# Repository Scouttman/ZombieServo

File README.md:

# ZombieServo
Motor Driver for some [aliexpress](https://www.aliexpress.com/item/1005004112490054.html) robotic serovos powered by simpleFOC and a STSPIN32g4
Runs simpleFOC forum post [here](https://community.simplefoc.com/t/zombie-servo-budget-high-torque-servo/4001)  
May also port the mit mini cheeta code to it if the torque control is good   
Position can be set with T i.e. set T6.28 will do one rotation (not sure why it is not a full rotation)  
The M command for simple foc is added but not tested

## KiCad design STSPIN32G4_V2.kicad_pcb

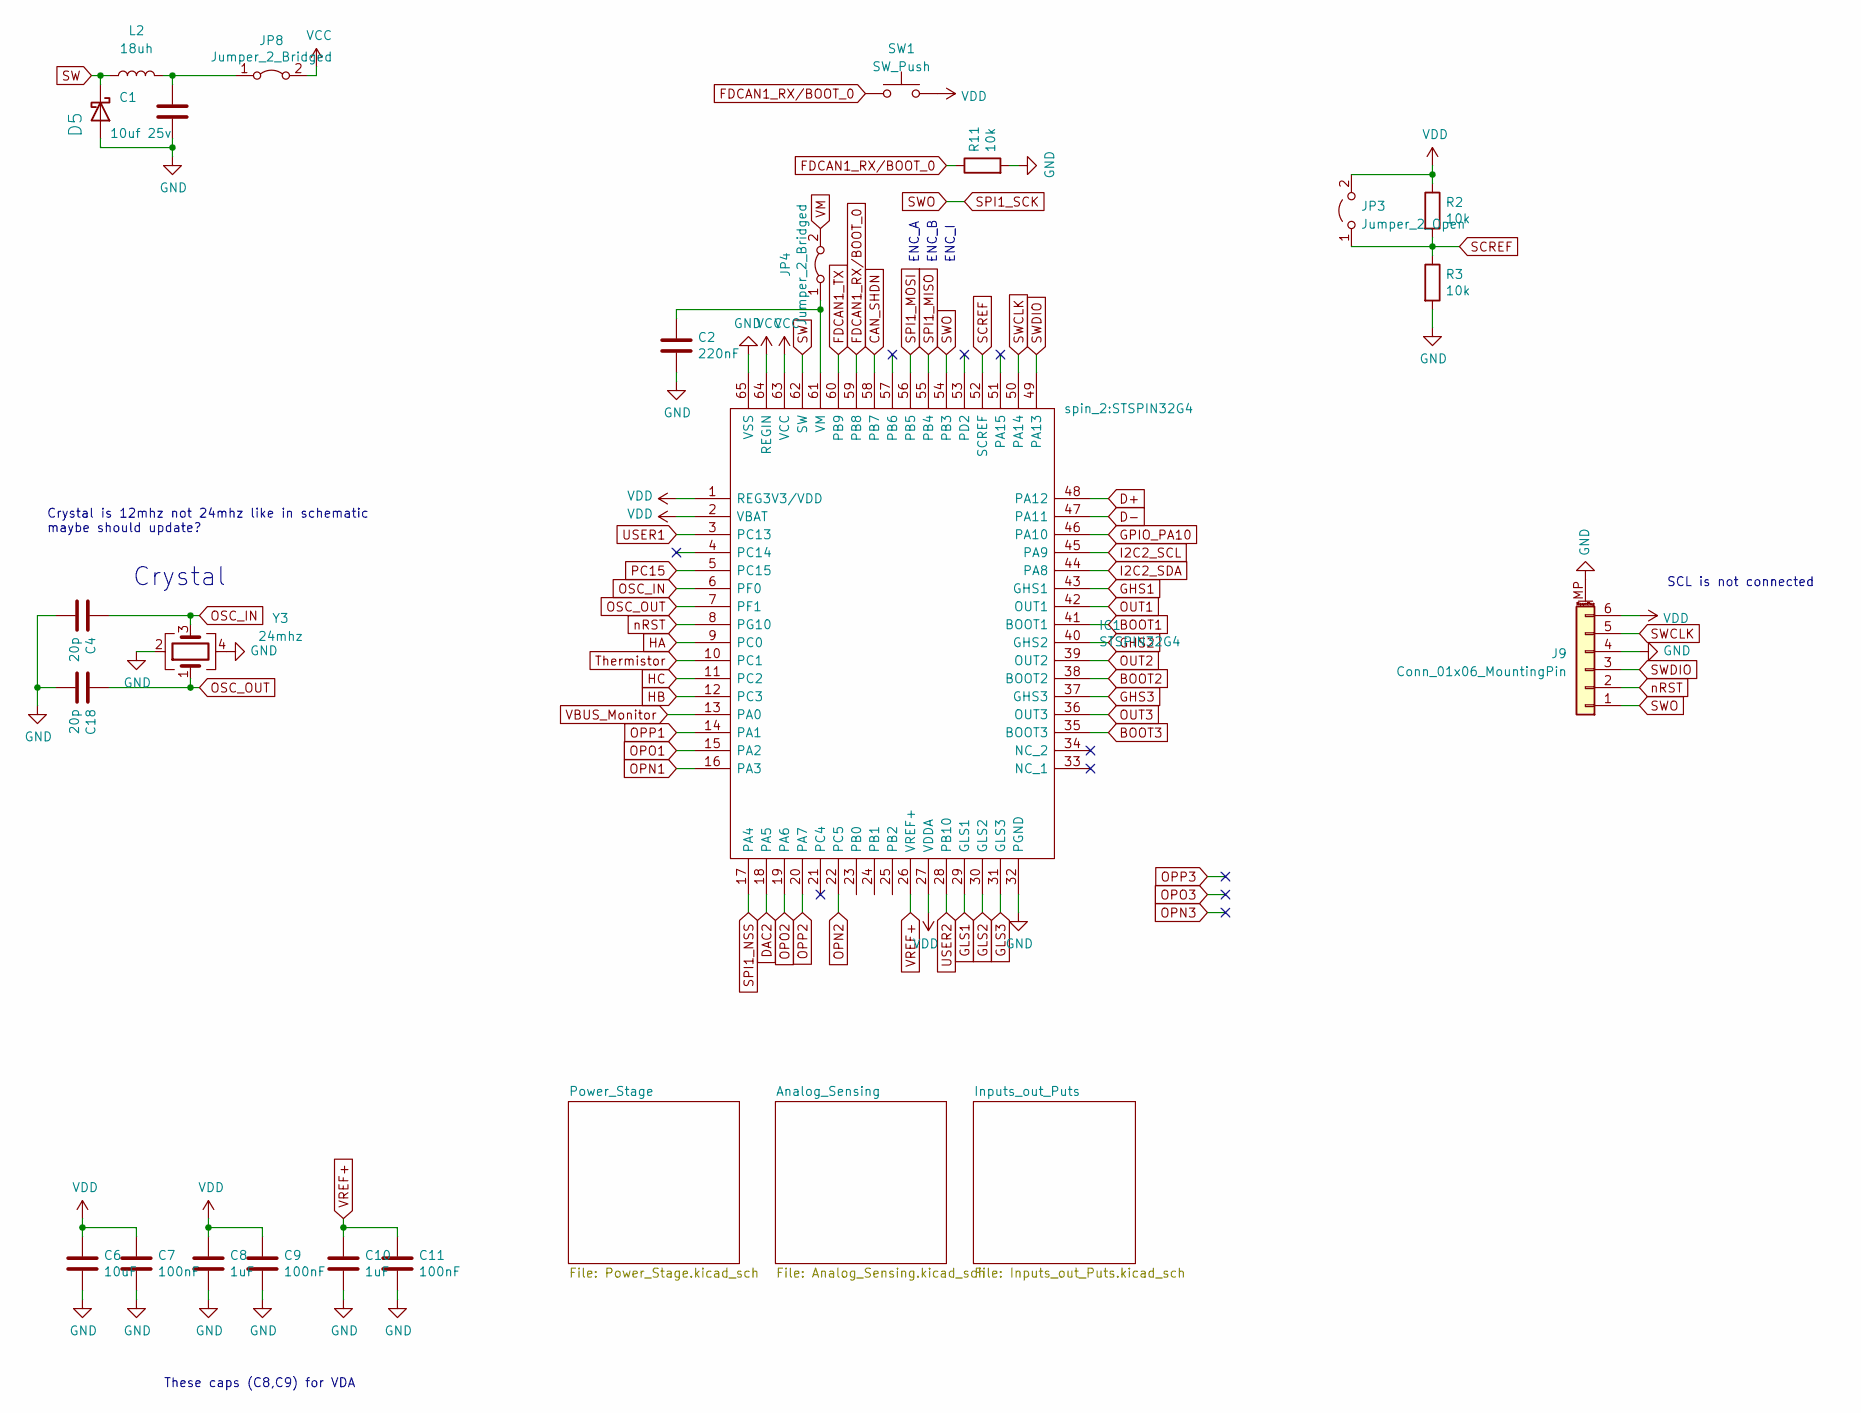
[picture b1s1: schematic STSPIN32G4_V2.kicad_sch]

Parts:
C1: 10uf 25v; C_0805_2012Metric
C2: 220nF; C_0805_2012Metric
C4, C18: 20p; C_0402_1005Metric
C6: 10uF; C_0805_2012Metric; LCSC Part C15850
C7, C9, C11: 100nF; C_0402_1005Metric
C8, C10: 1uF; C_0402_1005Metric
D5: SS210; D_SOD-323; LCSC C191023
IC1: STSPIN32G4; Manufacturer_Part_Number STSPIN32G4; Mouser Part Number 511-STSPIN32G4
J9: Conn_01x06_MountingPin; JST_SH_BM06B-SRSS-TB_1x06-1MP_P1.00mm_Vertical
JP3: Jumper_2_Open; SolderJumper-2_P1.3mm_Open_TrianglePad1.0x1.5mm
JP4, JP8: Jumper_2_Bridged; SolderJumper-2_P1.3mm_Bridged_RoundedPad1.0x1.5mm
L2: 18uh; L_1812_4532Metric; LCSC C394124
R2, R3, R11: 10k; R_0402_1005Metric
SW1: SW_Push; SolderJumper-2_P1.3mm_Open_RoundedPad1.0x1.5mm
Y3: 24mhz; Crystal_SMD_3225-4Pin_3.2x2.5mm; LCSC C9002

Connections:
BOOT1: IC1.41 (BOOT1); also elsewhere on the board
BOOT2: IC1.38 (BOOT2); also elsewhere on the board
BOOT3: IC1.35 (BOOT3); also elsewhere on the board
CAN_SHDN: IC1.58 (PB7); also elsewhere on the board
D+: IC1.48 (PA12); also elsewhere on the board
D-: IC1.47 (PA11); also elsewhere on the board
DAC2: IC1.18 (PA5)
FDCAN1_RX/BOOT_0: IC1.59 (PB8), R11.1, SW1.1; also elsewhere on the board
FDCAN1_TX: IC1.60 (PB9); also elsewhere on the board
GHS1: IC1.43 (GHS1); also elsewhere on the board
GHS2: IC1.40 (GHS2); also elsewhere on the board
GHS3: IC1.37 (GHS3); also elsewhere on the board
GLS1: IC1.29 (GLS1); also elsewhere on the board
GLS2: IC1.30 (GLS2); also elsewhere on the board
GLS3: IC1.31 (GLS3); also elsewhere on the board
GND: C1.2, C2.2, C4.2, C6.2, C7.2, C8.2, C9.2, C10.2, C11.2, C18.2, D5.2 (A), IC1.32 (PGND), IC1.65 (VSS), J9.4, J9.MP (MountPin), R3.2, R11.2, Y3.2, Y3.4; also elsewhere on the board
GPIO_PA10: IC1.46 (PA10); also elsewhere on the board
HA: IC1.9 (PC0); also elsewhere on the board
HB: IC1.12 (PC3); also elsewhere on the board
HC: IC1.11 (PC2); also elsewhere on the board
I2C2_SCL: IC1.45 (PA9); also elsewhere on the board
I2C2_SDA: IC1.44 (PA8); also elsewhere on the board
unnamed: C1.1, JP8.1 (A), L2.2
OPN1: IC1.16 (PA3); also elsewhere on the board
OPN2: IC1.22 (PC5); also elsewhere on the board
OPO1: IC1.15 (PA2); also elsewhere on the board
OPO2: IC1.19 (PA6); also elsewhere on the board
OPP1: IC1.14 (PA1); also elsewhere on the board
OPP2: IC1.20 (PA7); also elsewhere on the board
OSC_IN: C4.1, IC1.6 (PF0), Y3.3
OSC_OUT: C18.1, IC1.7 (PF1), Y3.1
OUT1: IC1.42 (OUT1); also elsewhere on the board
OUT2: IC1.39 (OUT2); also elsewhere on the board
OUT3: IC1.36 (OUT3); also elsewhere on the board
PC15: IC1.5 (PC15)
SCREF: IC1.52 (SCREF), JP3.1 (A), R2.2, R3.1
SPI1_MISO: IC1.55 (PB4); also elsewhere on the board
SPI1_MOSI: IC1.56 (PB5); also elsewhere on the board
SPI1_NSS: IC1.17 (PA4); also elsewhere on the board
SPI1_SCK: IC1.54 (PB3), J9.1; also elsewhere on the board
SW: D5.1 (K), IC1.62 (SW), L2.1
SWCLK: IC1.50 (PA14), J9.5
SWDIO: IC1.49 (PA13), J9.3
Thermistor: IC1.10 (PC1); also elsewhere on the board
USER1: IC1.3 (PC13); also elsewhere on the board
USER2: IC1.28 (PB10); also elsewhere on the board
VBUS_Monitor: IC1.13 (PA0); also elsewhere on the board
VCC: IC1.63 (VCC), IC1.64 (REGIN), JP8.2 (B)
VDD: C6.1, C7.1, C8.1, C9.1, IC1.1 (REG3V3/VDD), IC1.2 (VBAT), IC1.27 (VDDA), J9.6, JP3.2 (B), R2.1, SW1.2; also elsewhere on the board
VREF+: C10.1, C11.1, IC1.26 (VREF+); also elsewhere on the board
nRST: IC1.8 (PG10), J9.2

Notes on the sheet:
ENC_I
These caps (C8,C9) for VDA
ENC_B
Crystal
ENC_A
Crystal is 12mhz not 24mhz like in schematic maybe should update?
SCL is not connected

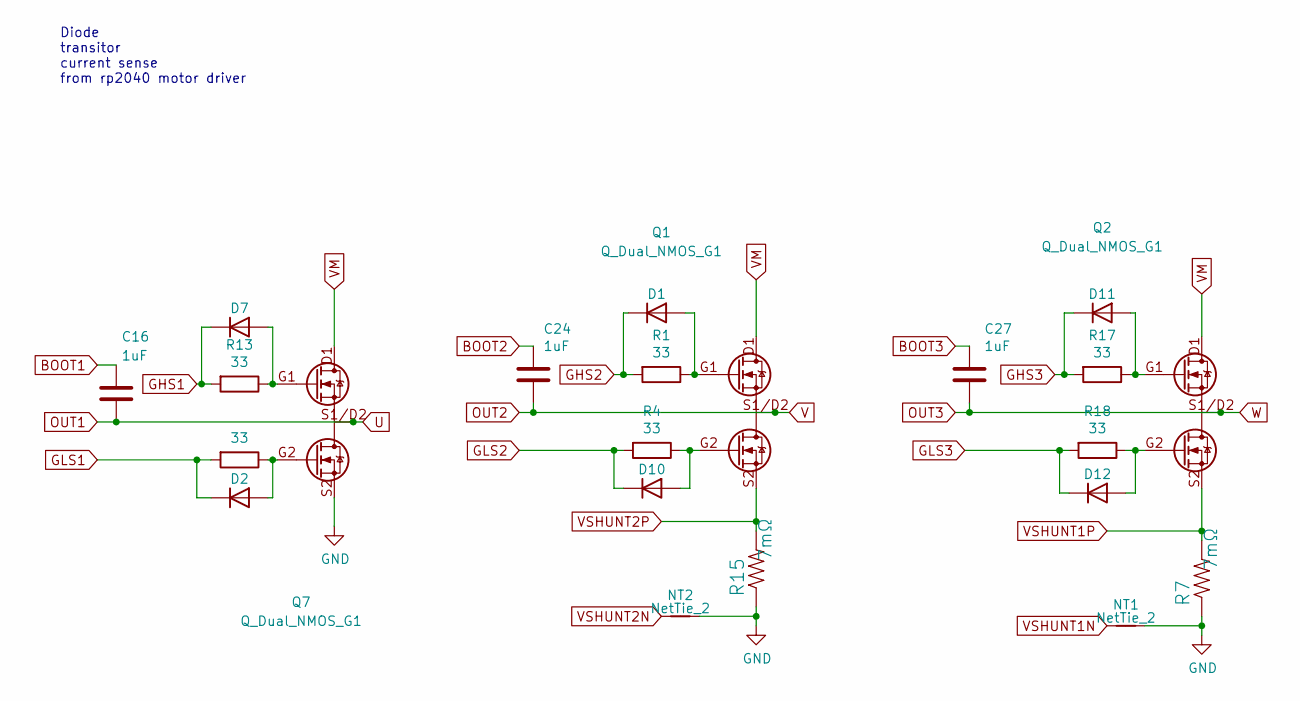
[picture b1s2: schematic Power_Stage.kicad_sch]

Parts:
C16, C24, C27: 1uF; C_0805_2012Metric; LCSC Part C28323
D1, D2, D7, D10, D11, D12: 1N4148WS; D_SOD-323; LCSC C2128
NT1, NT2: NetTie_2; NetTie-2_SMD_Pad0.5mm
Q1, Q2, Q7: Q_Dual_NMOS_G1; V-DFN3030-8 (Type K)
R1, R4, R13, R17, R18, R25: 33; R_0402_1005Metric
R7, R15: 7mΩ; R_1206_3216Metric; LCSC C76302

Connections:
BOOT1: C16.2; also elsewhere on the board
BOOT2: C24.2; also elsewhere on the board
BOOT3: C27.2; also elsewhere on the board
GHS1: D7.1 (K), R13.2; also elsewhere on the board
GHS2: D1.1 (K), R1.2; also elsewhere on the board
GHS3: D11.1 (K), R17.2; also elsewhere on the board
GLS1: D2.1 (K), R25.2; also elsewhere on the board
GLS2: D10.1 (K), R4.2; also elsewhere on the board
GLS3: D12.1 (K), R18.2; also elsewhere on the board
GND: NT1.2, NT2.2, Q7.S2, R7.1, R15.1; also elsewhere on the board
unnamed: D1.2 (A), Q1.G1, R1.1
unnamed: D2.2 (A), Q7.G2, R25.1
unnamed: D7.2 (A), Q7.G1, R13.1
unnamed: D10.2 (A), Q1.G2, R4.1
unnamed: D11.2 (A), Q2.G1, R17.1
unnamed: D12.2 (A), Q2.G2, R18.1
OUT1: C16.1, Q7.S1/D2; also elsewhere on the board
OUT2: C24.1, Q1.S1/D2; also elsewhere on the board
OUT3: C27.1, Q2.S1/D2; also elsewhere on the board
VSHUNT1N: NT1.1; also elsewhere on the board
VSHUNT1P: Q2.S2, R7.2; also elsewhere on the board
VSHUNT2N: NT2.1; also elsewhere on the board
VSHUNT2P: Q1.S2, R15.2; also elsewhere on the board

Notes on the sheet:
Diode transitor current sense from rp2040 motor driver

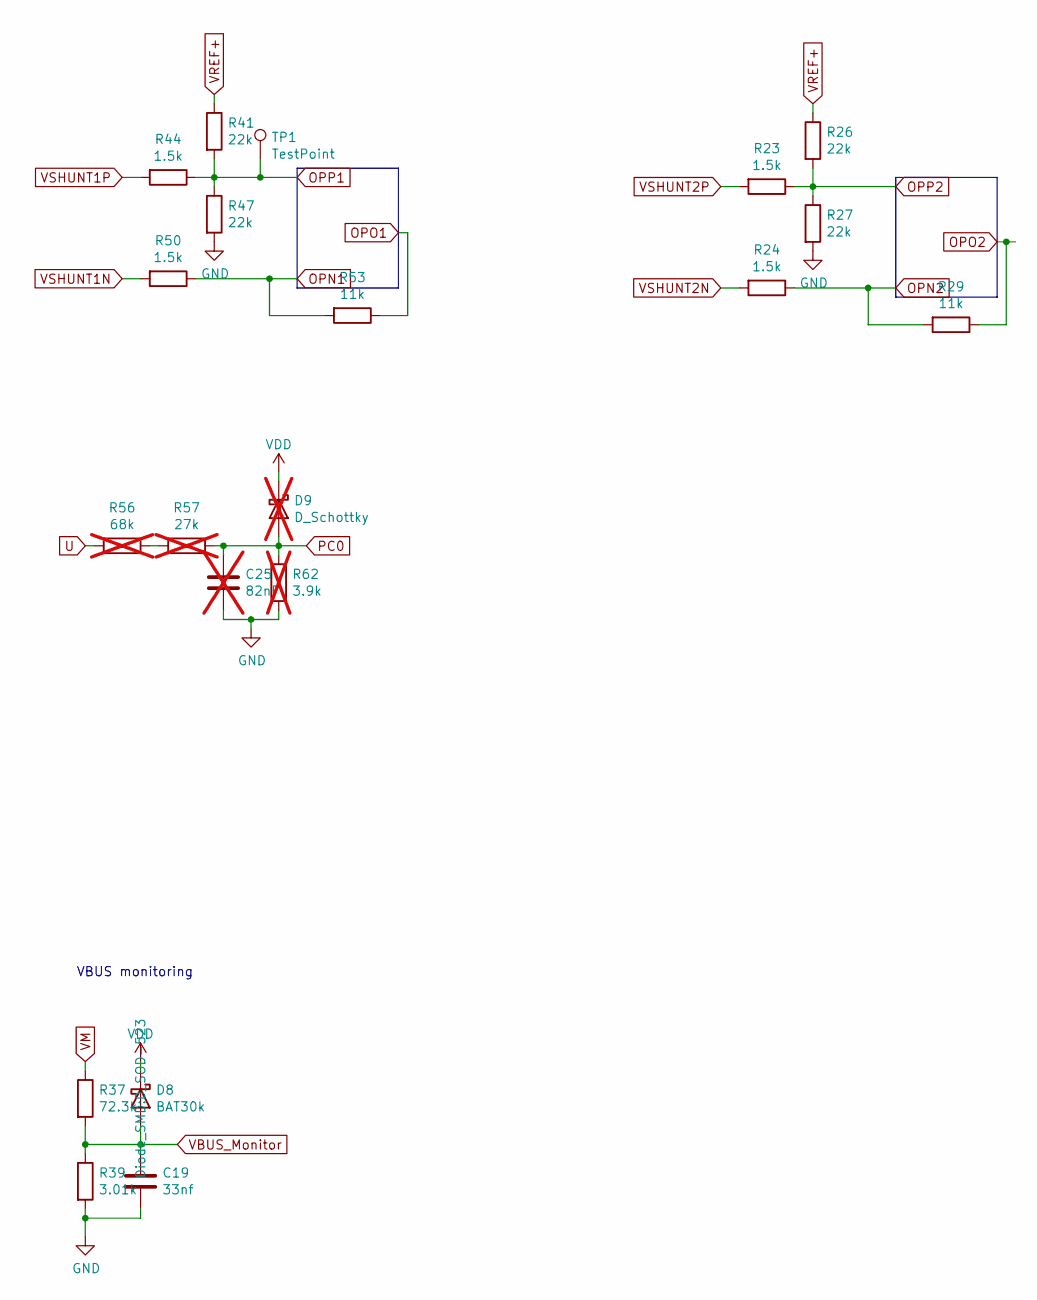
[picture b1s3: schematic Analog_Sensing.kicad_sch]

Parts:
C19: 33nf; C_0402_1005Metric
C25: 82nF; C_0402_1005Metric; not fitted
D8: BAT30k; D_SOD-523
D9: D_Schottky; D_SOD-523; not fitted
R23, R24, R44, R50: 1.5k; R_0402_1005Metric
R26, R27, R41, R47: 22k; R_0402_1005Metric
R29, R53: 11k; R_0402_1005Metric; LCSC C409665
R37: 72.3k; R_0402_1005Metric
R39: 3.01k; R_0402_1005Metric
R56: 68k; R_0402_1005Metric; not fitted
R57: 27k; R_0402_1005Metric; not fitted
R62: 3.9k; R_0402_1005Metric; not fitted
TP1: TestPoint; TestPoint_Pad_D2.0mm

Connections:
GND: C19.2, C25.2, R27.2, R39.2, R47.2, R62.2; also elsewhere on the board
unnamed: C25.1, D9.2 (A), R57.1, R62.1
unnamed: R56.1, R57.2
OPN1: R50.1, R53.2; also elsewhere on the board
OPN2: R24.1, R29.2; also elsewhere on the board
OPO1: R53.1; also elsewhere on the board
OPO2: R29.1; also elsewhere on the board
OPP1: R41.2, R44.1, R47.1, TP1.1; also elsewhere on the board
OPP2: R23.1, R26.2, R27.1; also elsewhere on the board
VBUS_Monitor: C19.1, D8.2 (A), R37.2, R39.1; also elsewhere on the board
VDD: D8.1 (K), D9.1 (K); also elsewhere on the board
VREF+: R26.1, R41.1; also elsewhere on the board
VSHUNT1N: R50.2; also elsewhere on the board
VSHUNT1P: R44.2; also elsewhere on the board
VSHUNT2N: R24.2; also elsewhere on the board
VSHUNT2P: R23.2; also elsewhere on the board

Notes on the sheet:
VBUS monitoring

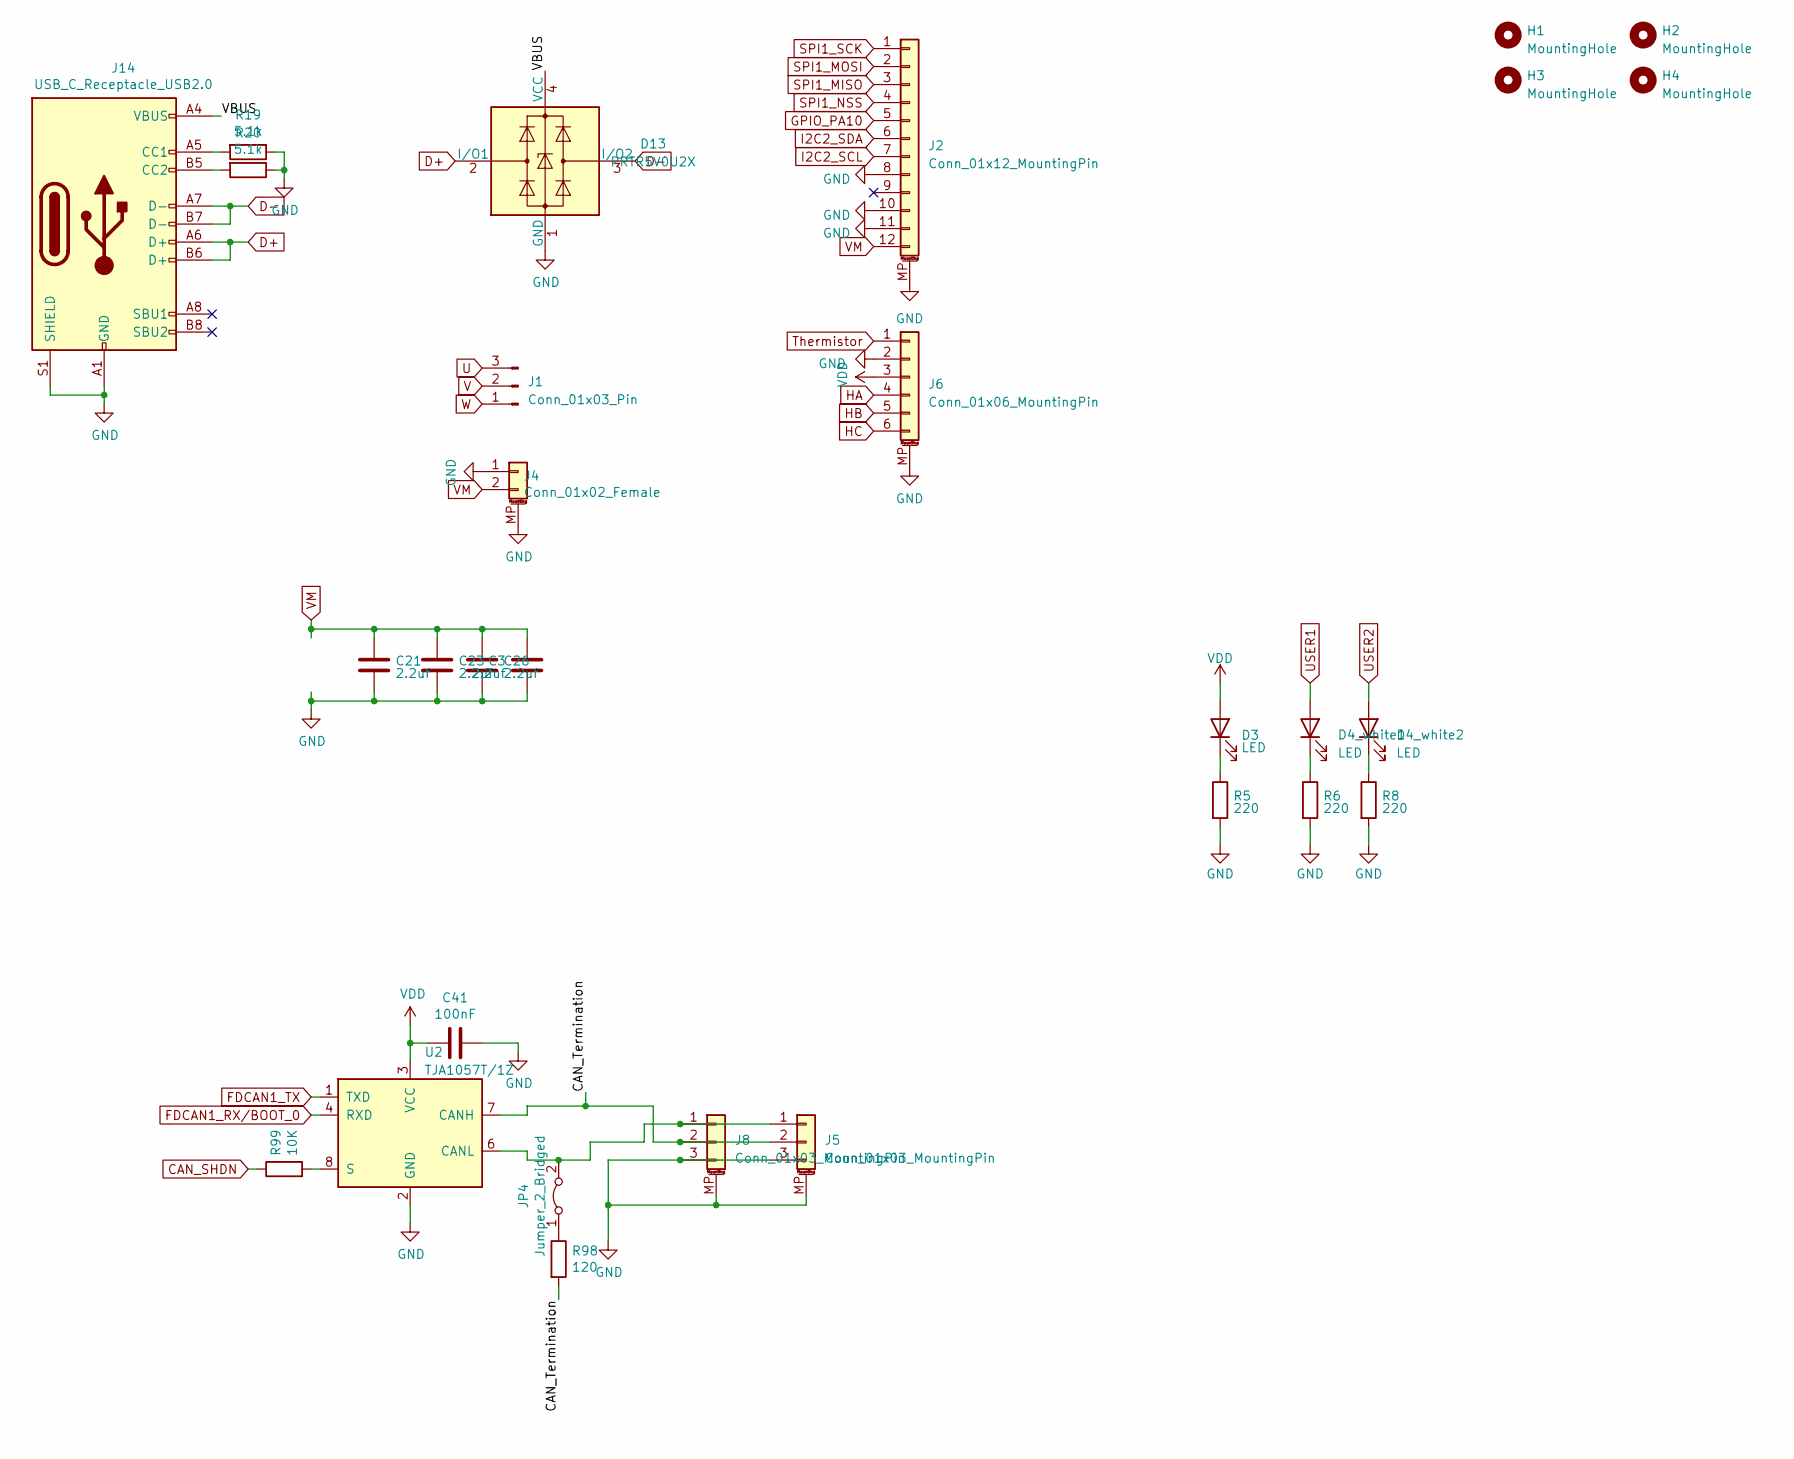
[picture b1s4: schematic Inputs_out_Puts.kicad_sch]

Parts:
C3, C21, C23, C26: 2.2uf; C_1206_3216Metric; LCSC Part C650969
C41: 100nF; C_0402_1005Metric
D3, D4_white1, D4_white2: LED; LED_0805_2012Metric
D13: PRTR5V0U2X; SOT-143
H1, H2, H3, H4: MountingHole; MountingHole_2.2mm_M2
J1: Conn_01x03_Pin; JST_XH_B3B-XH-AM_1x03_P2.50mm_Vertical
J2: Conn_01x12_MountingPin; 0.5K-A-12PBF; LCSC C2914207
J4: Conn_01x02_Female; PinHeader_1x02_P2.54mm_Vertical
J5, J8: Conn_01x03_MountingPin; JST_SH_BM03B-SRSS-TB_1x03-1MP_P1.00mm_Vertical
J6: Conn_01x06_MountingPin; PinHeader_1x06_P1.27mm_Vertical; LCSC C2904934
J14: USB_C_Receptacle_USB2.0; USB_C_Receptacle_XKB_U262-16XN-4BVC11; LCSC Part C165948
JP4: Jumper_2_Bridged; SolderJumper-2_P1.3mm_Bridged_RoundedPad1.0x1.5mm
R5, R6, R8: 220; R_0402_1005Metric
R19: 5.1k; R_0402_1005Metric
R20: 5.1k; R_0402_1005Metric; LCSC Part C23186
R98: 120; R_0402_1005Metric
R99: 10K; R_0402_1005Metric
U2: TJA1057T/1Z; SOIC-8_3.9x4.9mm_P1.27mm; LCSC C961484

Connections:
/Inputs_out_Puts/CAN_Termination: J5.2, J8.2, R98.2, U2.7 (CANH)
/Inputs_out_Puts/VBUS: D13.4 (VCC), J14.A4 (VBUS), J14.A9 (VBUS), J14.B4 (VBUS), J14.B9 (VBUS)
CAN_SHDN: R99.1; also elsewhere on the board
D+: D13.2 (I/O1), J14.A6 (D+), J14.B6 (D+); also elsewhere on the board
D-: D13.3 (I/O2), J14.A7 (D-), J14.B7 (D-); also elsewhere on the board
FDCAN1_RX/BOOT_0: U2.4 (RXD); also elsewhere on the board
FDCAN1_TX: U2.1 (TXD); also elsewhere on the board
GND: C3.2, C21.2, C23.2, C26.2, C41.1, D13.1 (GND), J2.8, J2.10, J2.11, J2.MP (MountPin), J4.1, J4.MP (MountPin), J5.3, J5.MP (MountPin), J6.2, J6.MP (MountPin), J8.3, J8.MP (MountPin), J14.A1 (GND), J14.A12 (GND), J14.B1 (GND), J14.B12 (GND), J14.S1 (SHIELD), R5.2, R6.2, R8.2, R19.1, R20.1, U2.2 (GND); also elsewhere on the board
GPIO_PA10: J2.5; also elsewhere on the board
HA: J6.4; also elsewhere on the board
HB: J6.5; also elsewhere on the board
HC: J6.6; also elsewhere on the board
I2C2_SCL: J2.7; also elsewhere on the board
I2C2_SDA: J2.6; also elsewhere on the board
unnamed: D3.1 (K), R5.1
unnamed: D4_white1.1 (K), R6.1
unnamed: D4_white2.1 (K), R8.1
unnamed: J14.A5 (CC1), R19.2
unnamed: J14.B5 (CC2), R20.2
unnamed: R99.2, U2.8 (S)
OUT1: J1.3; also elsewhere on the board
OUT2: J1.2; also elsewhere on the board
OUT3: J1.1; also elsewhere on the board
SPI1_MISO: J2.3; also elsewhere on the board
SPI1_MOSI: J2.2; also elsewhere on the board
SPI1_NSS: J2.4; also elsewhere on the board
SPI1_SCK: J2.1; also elsewhere on the board
Thermistor: J6.1; also elsewhere on the board
USER1: D4_white1.2 (A); also elsewhere on the board
USER2: D4_white2.2 (A); also elsewhere on the board
VDD: C41.2, D3.2 (A), J6.3, U2.3 (VCC); also elsewhere on the board

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
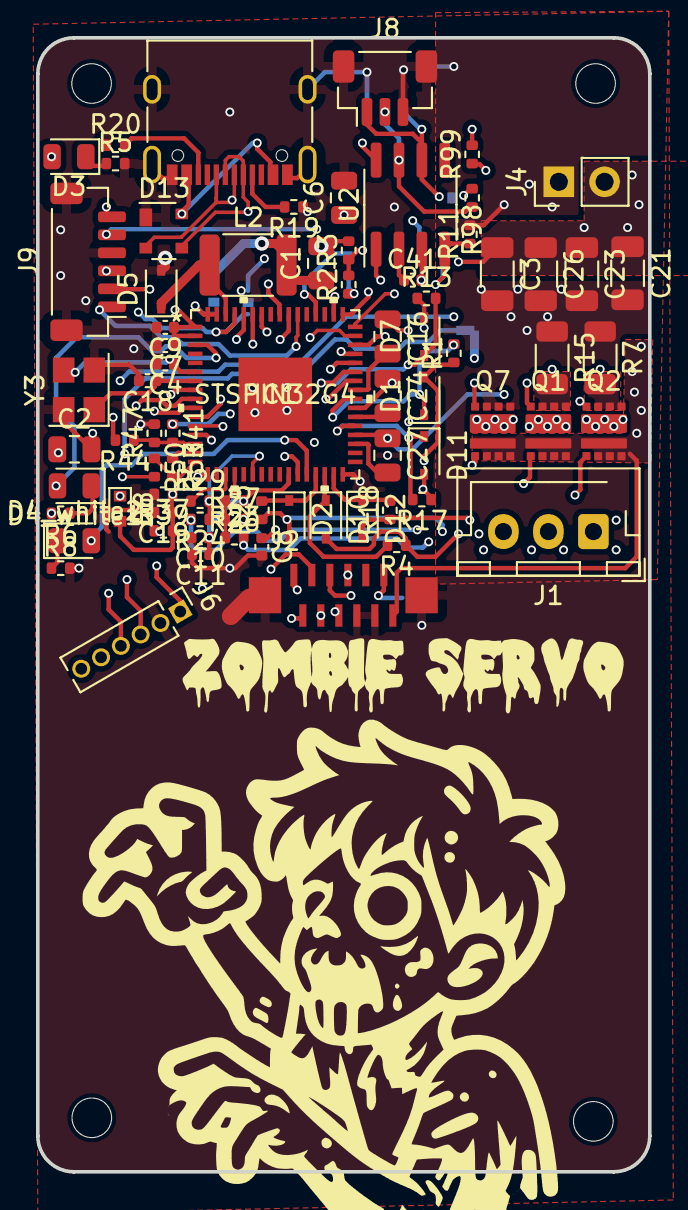
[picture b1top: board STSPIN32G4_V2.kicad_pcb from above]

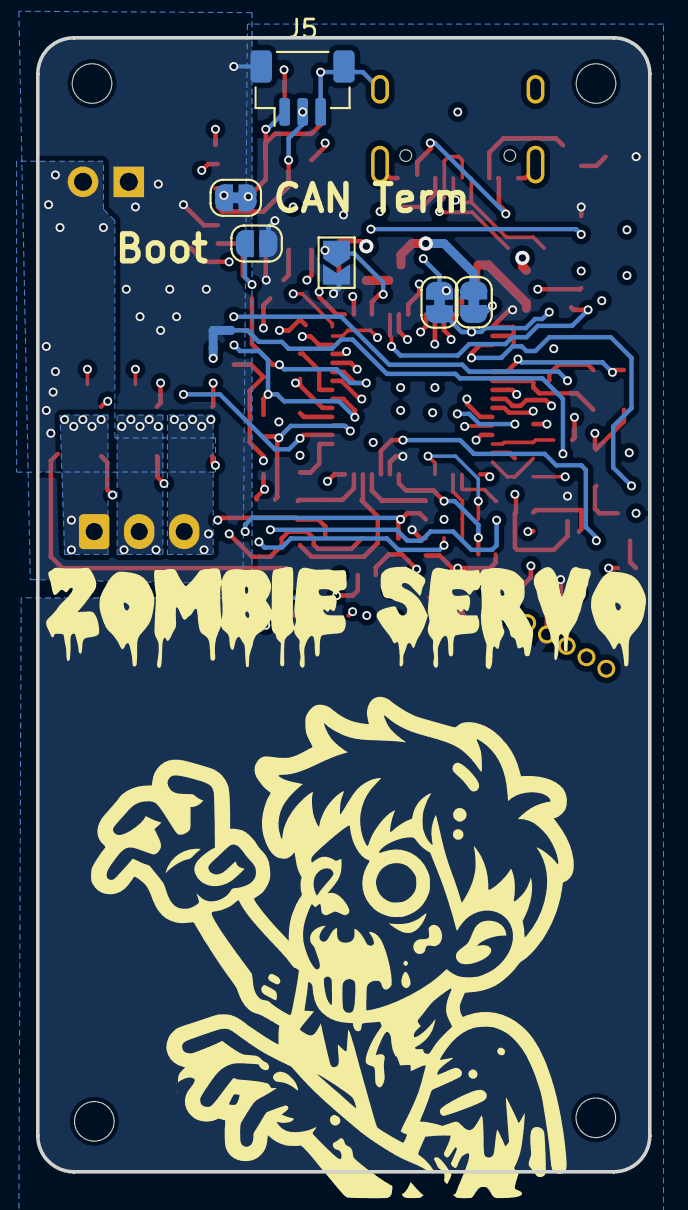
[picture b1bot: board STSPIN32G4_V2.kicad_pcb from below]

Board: 4 copper layers, 34.0 x 63.0 mm, 87 parts (8 on the bottom side), 71 nets.

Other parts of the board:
JP1: Jumper_2_Bridged; SolderJumper-2_P1.3mm_Bridged_RoundedPad1.0x1.5mm

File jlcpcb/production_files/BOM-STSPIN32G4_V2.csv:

Comment,Designator,Footprint,LCSC
Conn_01x03_MountingPin,J8,JST_SH_BM03B-SRSS-TB_1x03-1MP_P1.00mm_Vertical,C145955
Conn_01x06_MountingPin,J9,JST_SH_BM06B-SRSS-TB_1x06-1MP_P1.00mm_Vertical,C145958
20p,"C18,C4",C_0402_1005Metric,C1554
Q_Dual_NMOS_G1,"Q1,Q2,Q7",V-DFN3030-8 (Type K),C155503
33nf,C19,C_0402_1005Metric,C1585
10uf 25v,"C1,C6",C_0805_2012Metric,C15850
USB_C_Receptacle_USB2.0,J14,USB_C_Receptacle_XKB_U262-16XN-4BVC11,C165948
SS210,D5,D_SOD-323,C191023
1N4148WS,"D1,D10,D11,D12,D2,D7",D_SOD-323,C2128
LED,"D3,D4_white2",LED_0805_2012Metric,C2297
5.1k,R20,R_0402_1005Metric,C23186
120,R98,R_0402_1005Metric,C25079
220,"R5,R6,R8",R_0402_1005Metric,C25091
33,"R1,R13,R17,R18,R25,R4",R_0402_1005Metric,C25105
10k,"R11,R2,R3,R99",R_0402_1005Metric,C25744
22k,"R26,R27,R41,R47",R_0402_1005Metric,C25768
1.5k,"R23,R24,R44,R50",R_0402_1005Metric,C25867
5.1k,R19,R_0402_1005Metric,C25905
PRTR5V0U2X,D13,SOT-143,C2827688
1uF,"C16,C24,C27",C_0805_2012Metric,C28323
STSPIN32G4,IC1,STSPIN32G4,C2858620
Conn_01x06_MountingPin,J6,PinHeader_1x06_P1.27mm_Vertical,C2904934
Conn_01x12_MountingPin,J2,0.5K-A-12PBF,C2914207
BAT30k,D8,D_SOD-523,C2926449
100nF,"C11,C41,C7,C9",C_0402_1005Metric,C307331
18uh,L2,L_1812_4532Metric,C394124
11k,"R29,R53",R_0402_1005Metric,C409665
1uF,"C10,C8",C_0402_1005Metric,C52923
220nF,C2,C_0805_2012Metric,C5378
2.2uf,"C21,C23,C26,C3",C_1206_3216Metric,C650969
7mΩ,"R15,R7",R_1206_3216Metric,C76302
LED,D4_white1,LED_0805_2012Metric,C84256
24mhz,Y3,Crystal_SMD_3225-4Pin_3.2x2.5mm,C9002
TJA1057T/1Z,U2,SOIC-8_3.9x4.9mm_P1.27mm,C961484
Conn_01x02_Female,J4,PinHeader_1x02_P2.54mm_Vertical,
Jumper_2_Bridged,JP8,SolderJumper-2_P1.3mm_Bridged_RoundedPad1.0x1.5mm,
NetTie_2,NT1,NetTie-2_SMD_Pad0.5mm,
72.3k,R37,R_0402_1005Metric,
3.01k,R39,R_0402_1005Metric,
Jumper_2_Bridged,JP4,SolderJumper-2_P1.3mm_Bridged_RoundedPad1.0x1.5mm,
Jumper_2_Open,JP3,SolderJumper-2_P1.3mm_Open_TrianglePad1.0x1.5mm,
NetTie_2,NT2,NetTie-2_SMD_Pad0.5mm,
MountingHole,H3,MountingHole_2.2mm_M2,
MountingHole,H2,MountingHole_2.2mm_M2,
MountingHole,H1,MountingHole_2.2mm_M2,
MountingHole,H4,MountingHole_2.2mm_M2,
Conn_01x03_Pin,J1,JST_XH_B3B-XH-AM_1x03_P2.50mm_Vertical,
Conn_01x03_MountingPin,J5,JST_SH_BM03B-SRSS-TB_1x03-1MP_P1.00mm_Vertical,
SW_Push,SW1,SolderJumper-2_P1.3mm_Open_RoundedPad1.0x1.5mm,
Jumper_2_Bridged,JP1,SolderJumper-2_P1.3mm_Bridged_RoundedPad1.0x1.5mm,

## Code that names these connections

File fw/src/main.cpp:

#include <Arduino.h>
#include <SimpleFOC.h>
#include "drivers/stspin32g4/STSPIN32G4.h"
// #include "encoders/ma730/MA730.h"
#include "encoders/ma730/MagneticSensorMA730.h"

#define LED_WHITE PB_10 
#define LED_RED PC_13
#define MAG_CS PA4
#define MOIS_PIN PB5
#define MISO_PIN PB4
#define SCLK_PIN PB3
#define SSI_SSCK_FREQUENCY  10000       //SSI SSCK Clock frequency in Hz #TODO increase back to 100k

STSPIN32G4 driver = STSPIN32G4();
BLDCMotor motor = BLDCMotor(1); // for drive module
HallSensor sensor = HallSensor(PC0, PC2, PC3, 1);
MagneticSensorMA730 output_encoder = MagneticSensorMA730(MAG_CS);
// interrupt routine intialisation
void doA(){sensor.handleA();}
void doB(){sensor.handleB();}
void doC(){sensor.handleC();}

// External digital encoder
SPIClass SPI_1(MOIS_PIN, MISO_PIN, SCLK_PIN);
PIDController PID_ang{1000.0,0.0,0.0,0,5000}; // PID controller for the output angle

// angle set point variable
float target_angle = 0;
Commander command = Commander(Serial);
void doTarget(char* cmd) { command.scalar(&target_angle, cmd); }
void doMotor(char* cmd) { command.motor(&motor, cmd); }

int counter = 0;

void setup() {
  Serial.begin();
  Serial.println("Start");
  command.add('M',doMotor,"motor");
  // add target command T
  command.add('T', doTarget, "target angle");

  // setup timer 6 to count micro seconds as the micro second timer inside stduino is slow
  __HAL_RCC_TIM6_CLK_ENABLE();
  TIM6->PSC = HAL_RCC_GetPCLK1Freq()/1000000 - 1;
  TIM6->CR1 = TIM_CR1_CEN;

  /* Initialize all configured peripherals */
  pinMode(LED_WHITE, OUTPUT);
  pinMode(LED_RED, OUTPUT);
  
  // initialise encoder hardware
  sensor.init();
  sensor.enableInterrupts(doA, doB, doC);
  motor.linkSensor(&sensor);
  output_encoder.init(&SPI_1);

  // driver
  driver.voltage_power_supply = 17.0f;
  driver.voltage_limit = 17.0f;
  driver.init();
  motor.voltage_limit = driver.voltage_limit / 2.0f;
  motor.controller = MotionControlType::velocity;
  // set the torque control type
  motor.phase_resistance = 12.5; // 12.5 Ohms
  // set motion control loop to be used
  // motor.controller = MotionControlType::torque;
  motor.linkDriver(&driver);
  motor.init();

  motor.PID_velocity.P = 0.001f;
  motor.PID_velocity.I = 0.0f;
  motor.PID_velocity.D = 0;

  // initialize motor
  motor.init();
  // align encoder and start FOC
  motor.initFOC();
  // driver.voltage_limit = 6;

  Serial.println(F("Motor ready."));
  Serial.println(F("Set the target angle using serial terminal:"));
}

void loop() {
    // main FOC algorithm function
  motor.loopFOC();
  
  float vel_set = PID_ang(output_encoder.getAngle()-target_angle);
  motor.move(vel_set);
  if(driver.isFault()){
    digitalWrite(LED_WHITE, HIGH);
    digitalWrite(LED_RED, HIGH);
  }else{
    digitalWrite(LED_WHITE, LOW);
    digitalWrite(LED_RED, LOW);
  }
  // real-time monitoring calls
  motor.monitor();
  // real-time commander calls
  command.run();
  if(counter++%10000 == 0){
    Serial.print("Ang:");
    Serial.println(output_encoder.getAngle()); 

  }
  output_encoder.update();
}

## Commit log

2024-02-24 fw for board
2024-03-05 added the external angle sensor
2025-01-15 attempt at cleaning up

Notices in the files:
parts and their libraries:
Copyright 2021 Accelerated Designs. All rights reserved.
